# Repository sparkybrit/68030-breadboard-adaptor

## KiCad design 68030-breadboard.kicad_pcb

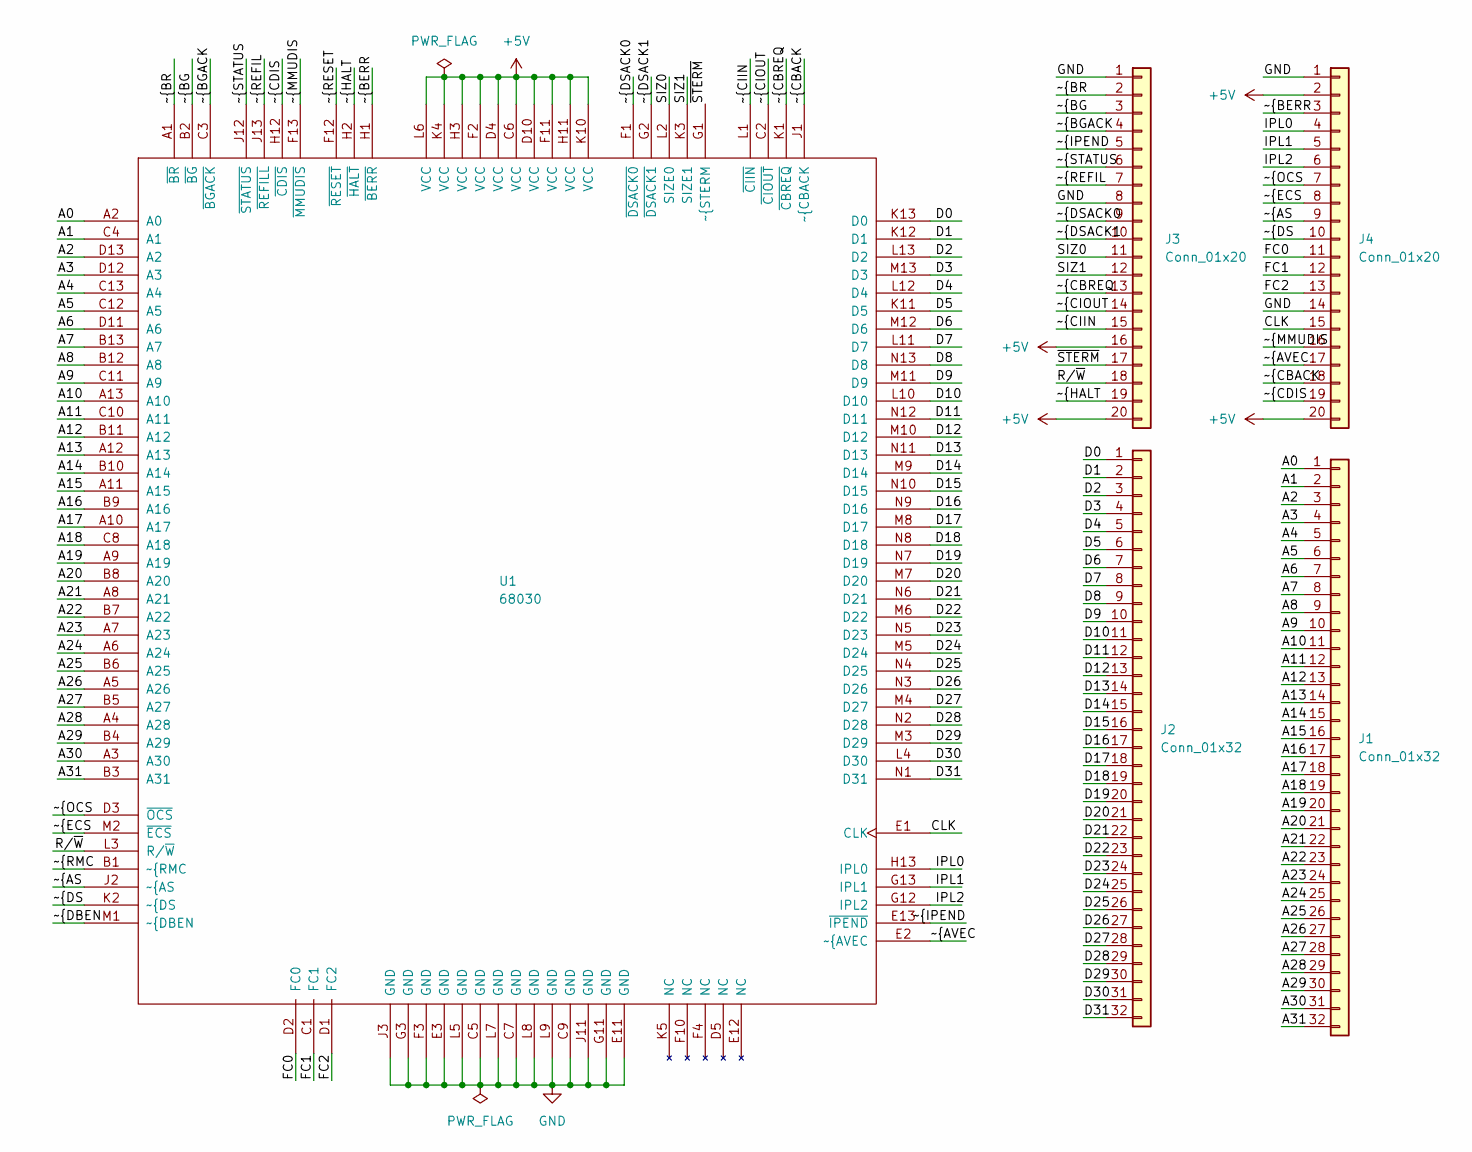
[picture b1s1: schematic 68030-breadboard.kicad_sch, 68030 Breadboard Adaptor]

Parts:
J1, J2: Conn_01x32; PinHeader_1x32_P2.54mm_Vertical
J3, J4: Conn_01x20; PinHeader_1x20_P2.54mm_Vertical
U1: 68030; PGA128

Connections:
+5V: J3.16, J3.20, J4.2, J4.20, U1.C6 (VCC), U1.D4 (VCC), U1.D10 (VCC), U1.F2 (VCC), U1.F11 (VCC), U1.H3 (VCC), U1.H11 (VCC), U1.K4 (VCC), U1.K10 (VCC), U1.L6 (VCC)
/A0: J1.1, U1.A2 (A0)
/A1: J1.2, U1.C4 (A1)
/A2: J1.3, U1.D13 (A2)
/A3: J1.4, U1.D12 (A3)
/A4: J1.5, U1.C13 (A4)
/A5: J1.6, U1.C12 (A5)
/A6: J1.7, U1.D11 (A6)
/A7: J1.8, U1.B13 (A7)
/A8: J1.9, U1.B12 (A8)
/A9: J1.10, U1.C11 (A9)
/A10: J1.11, U1.A13 (A10)
/A11: J1.12, U1.C10 (A11)
/A12: J1.13, U1.B11 (A12)
/A13: J1.14, U1.A12 (A13)
/A14: J1.15, U1.B10 (A14)
/A15: J1.16, U1.A11 (A15)
/A16: J1.17, U1.B9 (A16)
/A17: J1.18, U1.A10 (A17)
/A18: J1.19, U1.C8 (A18)
/A19: J1.20, U1.A9 (A19)
/A20: J1.21, U1.B8 (A20)
/A21: J1.22, U1.A8 (A21)
/A22: J1.23, U1.B7 (A22)
/A23: J1.24, U1.A7 (A23)
/A24: J1.25, U1.A6 (A24)
/A25: J1.26, U1.B6 (A25)
/A26: J1.27, U1.A5 (A26)
/A27: J1.28, U1.B5 (A27)
/A28: J1.29, U1.A4 (A28)
/A29: J1.30, U1.B4 (A29)
/A30: J1.31, U1.A3 (A30)
/A31: J1.32, U1.B3 (A31)
/CLK: J4.15, U1.E1 (CLK)
/D0: J2.1, U1.K13 (D0)
/D1: J2.2, U1.K12 (D1)
/D2: J2.3, U1.L13 (D2)
/D3: J2.4, U1.M13 (D3)
/D4: J2.5, U1.L12 (D4)
/D5: J2.6, U1.K11 (D5)
/D6: J2.7, U1.M12 (D6)
/D7: J2.8, U1.L11 (D7)
/D8: J2.9, U1.N13 (D8)
/D9: J2.10, U1.M11 (D9)
/D10: J2.11, U1.L10 (D10)
/D11: J2.12, U1.N12 (D11)
/D12: J2.13, U1.M10 (D12)
/D13: J2.14, U1.N11 (D13)
/D14: J2.15, U1.M9 (D14)
/D15: J2.16, U1.N10 (D15)
/D16: J2.17, U1.N9 (D16)
/D17: J2.18, U1.M8 (D17)
/D18: J2.19, U1.N8 (D18)
/D19: J2.20, U1.N7 (D19)
/D20: J2.21, U1.M7 (D20)
/D21: J2.22, U1.N6 (D21)
/D22: J2.23, U1.M6 (D22)
/D23: J2.24, U1.N5 (D23)
/D24: J2.25, U1.M5 (D24)
/D25: J2.26, U1.N4 (D25)
/D26: J2.27, U1.N3 (D26)
/D27: J2.28, U1.M4 (D27)
/D28: J2.29, U1.N2 (D28)
/D29: J2.30, U1.M3 (D29)
/D30: J2.31, U1.L4 (D30)
/D31: J2.32, U1.N1 (D31)
/FC0: J4.11, U1.D2 (FC0)
/FC1: J4.12, U1.C1 (FC1)
/FC2: J4.13, U1.D1 (FC2)
/IPL0: J4.4, U1.H13 (IPL0)
/IPL1: J4.5, U1.G13 (IPL1)
/IPL2: J4.6, U1.G12 (IPL2)
/R/~W: J3.18, U1.L3 (R/~W)
/SIZ0: J3.11, U1.L2 (SIZE0)
/SIZ1: J3.12, U1.K3 (SIZE1)
/~AS: J4.9, U1.J2 (~{AS)
/~AVEC: J4.17, U1.E2 (~{AVEC)
/~BERR: J4.3, U1.H1 (~BERR)
/~BGACK: J3.4, U1.C3 (~BGACK)
/~BG: J3.3, U1.B2 (~BG)
/~BR: J3.2, U1.A1 (~BR)
/~CBACK: J4.18, U1.J1 (~{CBACK)
/~CBREQ: J3.13, U1.K1 (~CBREQ)
/~CDIS: J4.19, U1.H12 (~CDIS)
/~CIIN: J3.15, U1.L1 (~CIIN)
/~CIOUT: J3.14, U1.C2 (~CIOUT)
/~DBEN: U1.M1 (~{DBEN)
/~DSACK0: J3.9, U1.F1 (~DSACK0)
/~DSACK1: J3.10, U1.G2 (~DSACK1)
/~DS: J4.10, U1.K2 (~{DS)
/~ECS: J4.8, U1.M2 (~ECS)
/~HALT: J3.19, U1.H2 (~HALT)
/~IPEND: J3.5, U1.E13 (~IPEND)
/~MMUDIS: J4.16, U1.F13 (~MMUDIS)
/~OCS: J4.7, U1.D3 (~OCS)
/~REFIL: J3.7, U1.J13 (~REFILL)
/~RESET: U1.F12 (~RESET)
/~RMC: U1.B1 (~{RMC)
/~STATUS: J3.6, U1.J12 (~STATUS)
/~STERM: J3.17, U1.G1 (~{STERM)
GND: J3.1, J3.8, J4.1, J4.14, U1.C5 (GND), U1.C7 (GND), U1.C9 (GND), U1.E3 (GND), U1.E11 (GND), U1.F3 (GND), U1.G3 (GND), U1.G11 (GND), U1.J3 (GND), U1.J11 (GND), U1.L5 (GND), U1.L7 (GND), U1.L8 (GND), U1.L9 (GND)

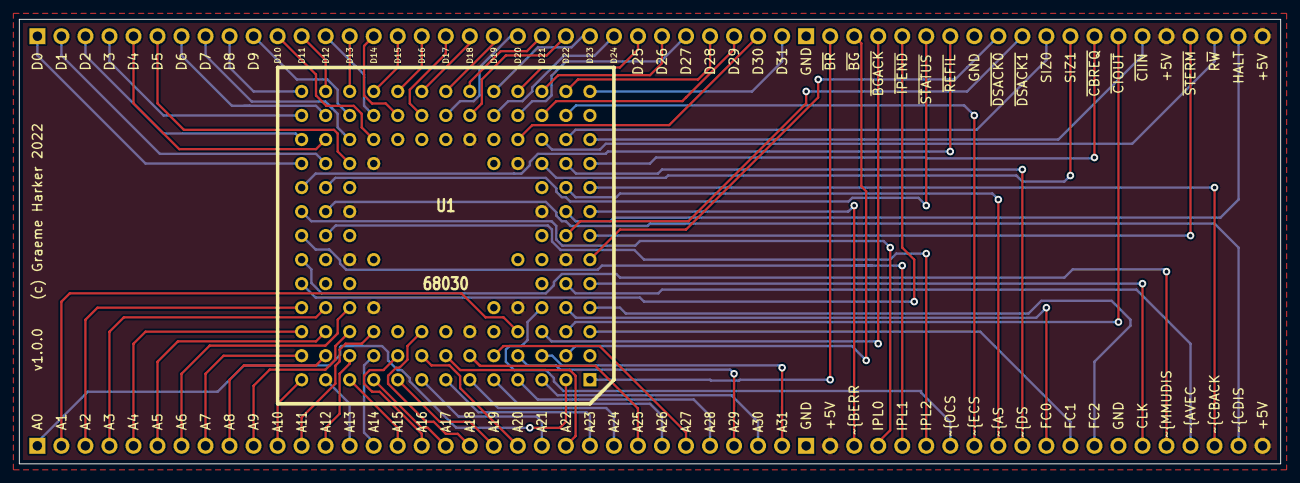
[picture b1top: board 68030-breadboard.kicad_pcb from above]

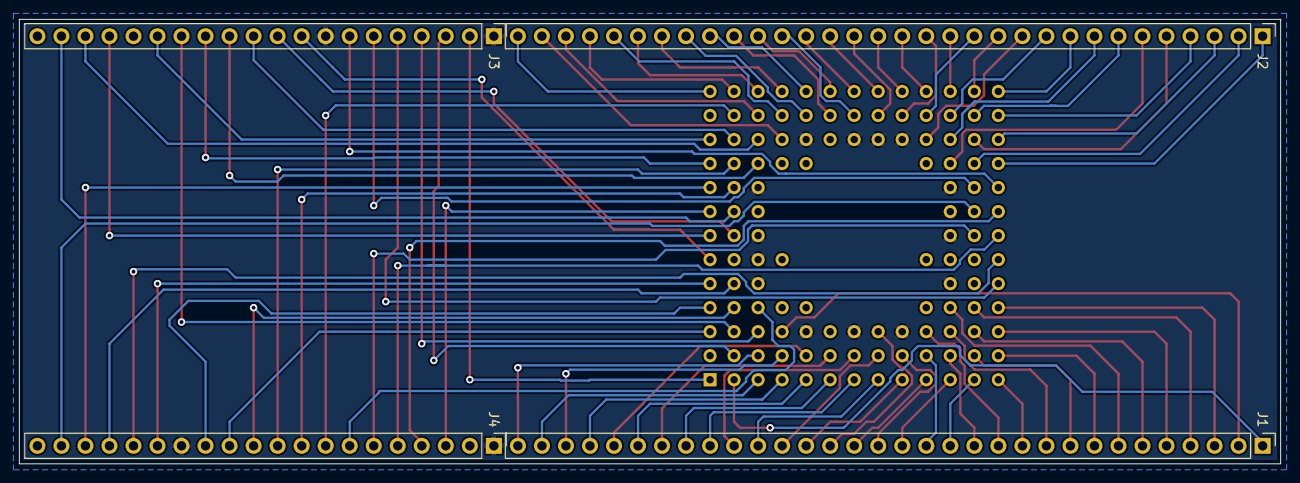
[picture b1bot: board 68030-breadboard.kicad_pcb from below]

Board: 2 copper layers, 133.3 x 47.0 mm, 5 parts (4 on the bottom side), 98 nets.

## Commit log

2022-11-01 Add fp-info-cache to .gitignore
2023-03-10 Add .DS_Store to .gitignore
2023-06-22 upgrade to KiCad v7
